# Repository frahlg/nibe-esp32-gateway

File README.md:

# NIBE ESP32 Gateway

An open-hardware ESP32-S3 board that plugs into the accessory bus of a NIBE
F-series heat pump (the MODBUS 40 port) and gives you local Wi-Fi access to it.
One 4-core cable to the pump carries both the data and the power. Order it fully
assembled from JLCPCB and print the box yourself.

Designed for the NIBE **F750**; the same port exists on F370, F470, F730,
F1145, F1155, F1245, F1255, SMO 40 and several VVM models.

> **Status: rev 1.0, design complete, not yet built.** The schematic and board
> pass KiCad's ERC and DRC, and every part was in stock at JLCPCB on 2026-11-25.
> Nobody has built a board or tested one on a heat pump yet. The ESPHome
> firmware in [`firmware/`](firmware) compiles but has not run on hardware. You can try
> it on the pump first with a [test rig](docs/test-rig.md) of shop-bought parts.

## What it does

- Talks to the heat pump on RS-485 the way a NIBE MODBUS 40 accessory does, so
  it works with the existing open-source gateways:
  [esphome-nibe](https://github.com/elupus/esphome-nibe),
  [NibeGW](https://www.openhab.org/addons/bindings/nibeheatpump/),
  [nibegw-esp](https://github.com/nptr/nibegw-esp) and the Home Assistant
  [Nibe Heat Pump](https://www.home-assistant.io/integrations/nibe_heatpump/)
  integration.
- Runs from the pump's own 12 V supply (AA3-X4:12), like MODBUS 40.
- USB-C for flashing and bench power.
- Protected against surges, reverse polarity and shorts on the pump cable.

| | |
|---|---|
| MCU | ESP32-S3-WROOM-1-N8R2 (Wi-Fi, Bluetooth LE, 8 MB flash, 2 MB PSRAM) |
| Bus | THVD1450 RS-485 transceiver, ±18 kV ESD, fail-safe receiver, PSM712 TVS, 120 Ω terminator on a cuttable jumper |
| Power | 12 V from the pump (9–18 V) or 5 V USB-C, TPS62933 buck to 3.3 V, PTC fuse, TVS |
| Connectors | 4-pin 3.5 mm pluggable terminal (12V, A, B, GND), USB-C |
| Other | RESET and BOOT buttons, PWR/STAT/BUS LEDs, unfitted 6-pin expansion header |
| Board | 50 × 58 mm, 2 layers |
| Box | 55 × 63 × 18 mm, two printed parts, 4 × M3 screws |

## Wiring

| Gateway | F750 terminal AA3-X4 |
|---|---|
| 12V | 12 |
| A | 11 |
| B | 10 |
| GND | 9 |

Then tick MODBUS 40 in the service menu (5.2 or 5.2.4). Full steps, with
safety notes, are in [docs/installation.md](docs/installation.md).

## Make one

1. **Board:** upload the files in [`hardware/production/`](hardware/production)
   to JLCPCB with assembly. See [docs/ordering.md](docs/ordering.md).
2. **Box:** print [`enclosure/base.stl`](enclosure/base.stl) and
   [`enclosure/lid.stl`](enclosure/lid.stl) in PETG or PLA, no supports.
3. **Firmware:** start from [`firmware/`](firmware) (pin map and an ESPHome
   configuration).
4. **Install:** [docs/installation.md](docs/installation.md).

## Documents

| | |
|---|---|
| [docs/installation.md](docs/installation.md) | Wiring to the F750, enabling MODBUS 40, troubleshooting |
| [docs/ordering.md](docs/ordering.md) | JLCPCB order, loose parts, printing, assembly |
| [docs/test-rig.md](docs/test-rig.md) | Try the firmware on the pump before you order boards, with an M5Stack Atom + Tail485 or a DevKitC rig |
| [docs/protocol.md](docs/protocol.md) | The NIBE accessory bus: electrical layer, frames, commands, timing, sources |
| [docs/design-notes.md](docs/design-notes.md) | Why each part is there, known gaps |
| [docs/schematic.pdf](docs/schematic.pdf) | Schematic |
| [hardware/README.md](hardware/README.md) | How the board is generated and checked |
| [enclosure/README.md](enclosure/README.md) | The box |
| [firmware/README.md](firmware/README.md) | Pin map, first flash |

## Repository

```
hardware/    board: Python source, generated KiCad project, production files
enclosure/   printable box: CadQuery source, STL and STEP
firmware/    pin map and a starting ESPHome configuration
docs/        installation, ordering, protocol, design notes, images
```

The board is generated from Python and checked by KiCad on every build, so a
change is: edit `hardware/generator/circuit.py`, run `hardware/build.sh`, read the
check results. See [hardware/README.md](hardware/README.md).

## Credits

This board stands on work by the NIBE open-source community: the openHAB
NibeGW gateway, esphome-nibe (elupus), NibePi (anerdins), nibegw-esp (nptr) and
the nibe Python library (yozik04). The protocol notes in
[docs/protocol.md](docs/protocol.md) come from their code and issue threads.

NIBE and MODBUS 40 are trademarks of NIBE AB. This project is not made or
endorsed by NIBE. Connecting third-party hardware to your heat pump is at your
own risk.

## Licence

- Hardware (board, schematic, enclosure): [CERN-OHL-P-2.0](LICENSE-HARDWARE)
- Software and scripts: [MIT](LICENSE-SOFTWARE)

---

### På svenska

Ett öppet ESP32-S3-kort som kopplas till tillbehörsbussen (MODBUS 40-porten) på
NIBE:s F-serie, till exempel F750. En 4-ledarkabel till plint AA3-X4 (12V, A, B,
GND) ger både data och ström. Kortet beställs färdigmonterat från JLCPCB med
filerna i `hardware/production/`, och lådan skrivs ut med 3D-skrivare från
`enclosure/`. Revision 1.0 är färdigritad och kontrollerad i KiCad men ännu inte
tillverkad eller testad på en värmepump. Mjukvaran är nästa steg.

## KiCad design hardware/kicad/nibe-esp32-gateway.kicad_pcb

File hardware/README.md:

# Hardware

The board is described in Python and turned into a normal KiCad 9 project. You
can open `kicad/nibe-esp32-gateway.kicad_pro` in KiCad and look at or edit
everything, but the next build overwrites hand edits. Change the Python, not the
KiCad files.

```
hardware/
├── build.sh                 build everything inside the official KiCad 9 Docker image
├── fetch-3d-models.sh       download KiCad 3D models (only for renders and STEP)
├── generator/
│   ├── circuit.py           THE CIRCUIT: parts, nets, schematic and board positions
│   ├── parts.py             part catalogue: symbol, footprint, LCSC number
│   ├── build.py             schematic, netlist check, ERC
│   ├── build_pcb.py         placement, routing, ground pours, silkscreen, DRC
│   ├── build_fab.py         Gerbers, drill, BOM, CPL, PDFs, STEP, renders
│   ├── schgen.py            writes .kicad_sch files
│   ├── pcbgen.py            pcbnew helpers
│   ├── router.py            small A* router (two layers, 45°, vias)
│   ├── fab.py               JLCPCB BOM/CPL and rotation corrections
│   ├── sexp.py              S-expression reader/writer
│   └── tools/               pins.py, footprint_pads.py, check_stock.py
├── kicad/                   generated KiCad project (schematic, board, project)
└── production/              generated files to order the board
```

## Build

You need Docker. Nothing else is installed on your machine.

```bash
cd hardware
./fetch-3d-models.sh   # optional, once: 3D models for renders and the STEP file
./build.sh             # schematic + board + production files
```

`./build.sh sch`, `./build.sh pcb` and `./build.sh fab` run one step each.

## What a build checks

Each step stops or reports when something is wrong:

1. **Netlist check.** The schematic is exported to a netlist with `kicad-cli`
   and compared pin by pin with `circuit.py`. Any difference stops the build.
2. **ERC** on the schematic (must report 0 issues).
3. **Routing.** Every net must route; failures are listed.
4. **DRC with schematic parity** on the board: clearances, unconnected items,
   and that the board matches the schematic. The build prints `DRC summary:
   clean` when all is well.

The enclosure has its own fit check against the board's STEP file (see
[../enclosure](../enclosure)).

## How the board is made

- **Schematic.** Every pin gets a short wire and a net label or power symbol.
  That keeps the generated drawing readable and easy to check.
- **Placement** is hand-written in `circuit.py`, in millimetres from the top-left
  corner of the board.
- **Routing.** A small grid router (`router.py`) routes one net at a time on a
  0.1 mm grid, or 0.05 mm next to 0.5 mm pitch pins. Power nets get wider
  tracks. Ground is not routed: both layers have a ground pour, each ground pad
  gets its own via just outside the pad, and stitching vias tie the pours
  together. The buck's SW and VBUCK nets are copper areas (`BUCK_ZONES` in
  `circuit.py`), not routed tracks.
- **No via in a pad.** The router never puts a via within 0.15 mm of an SMD pad
  of any net, and the build prints `via-in-pad check: 0 vias ...`.
- **Design rules** follow JLCPCB's standard 2-layer process: 0.2 mm clearance,
  0.25 mm signal tracks, 0.5–0.6 mm power tracks, 0.3/0.6 mm vias.

## Changing the circuit

1. Edit `circuit.py` (and `parts.py` for a new part).
2. `./build.sh` and read the output: netlist, ERC, routing, DRC.
3. Look at `docs/images/pcb-top.png` and `production/*.pdf`.
4. `python3 generator/tools/check_stock.py` before you order.

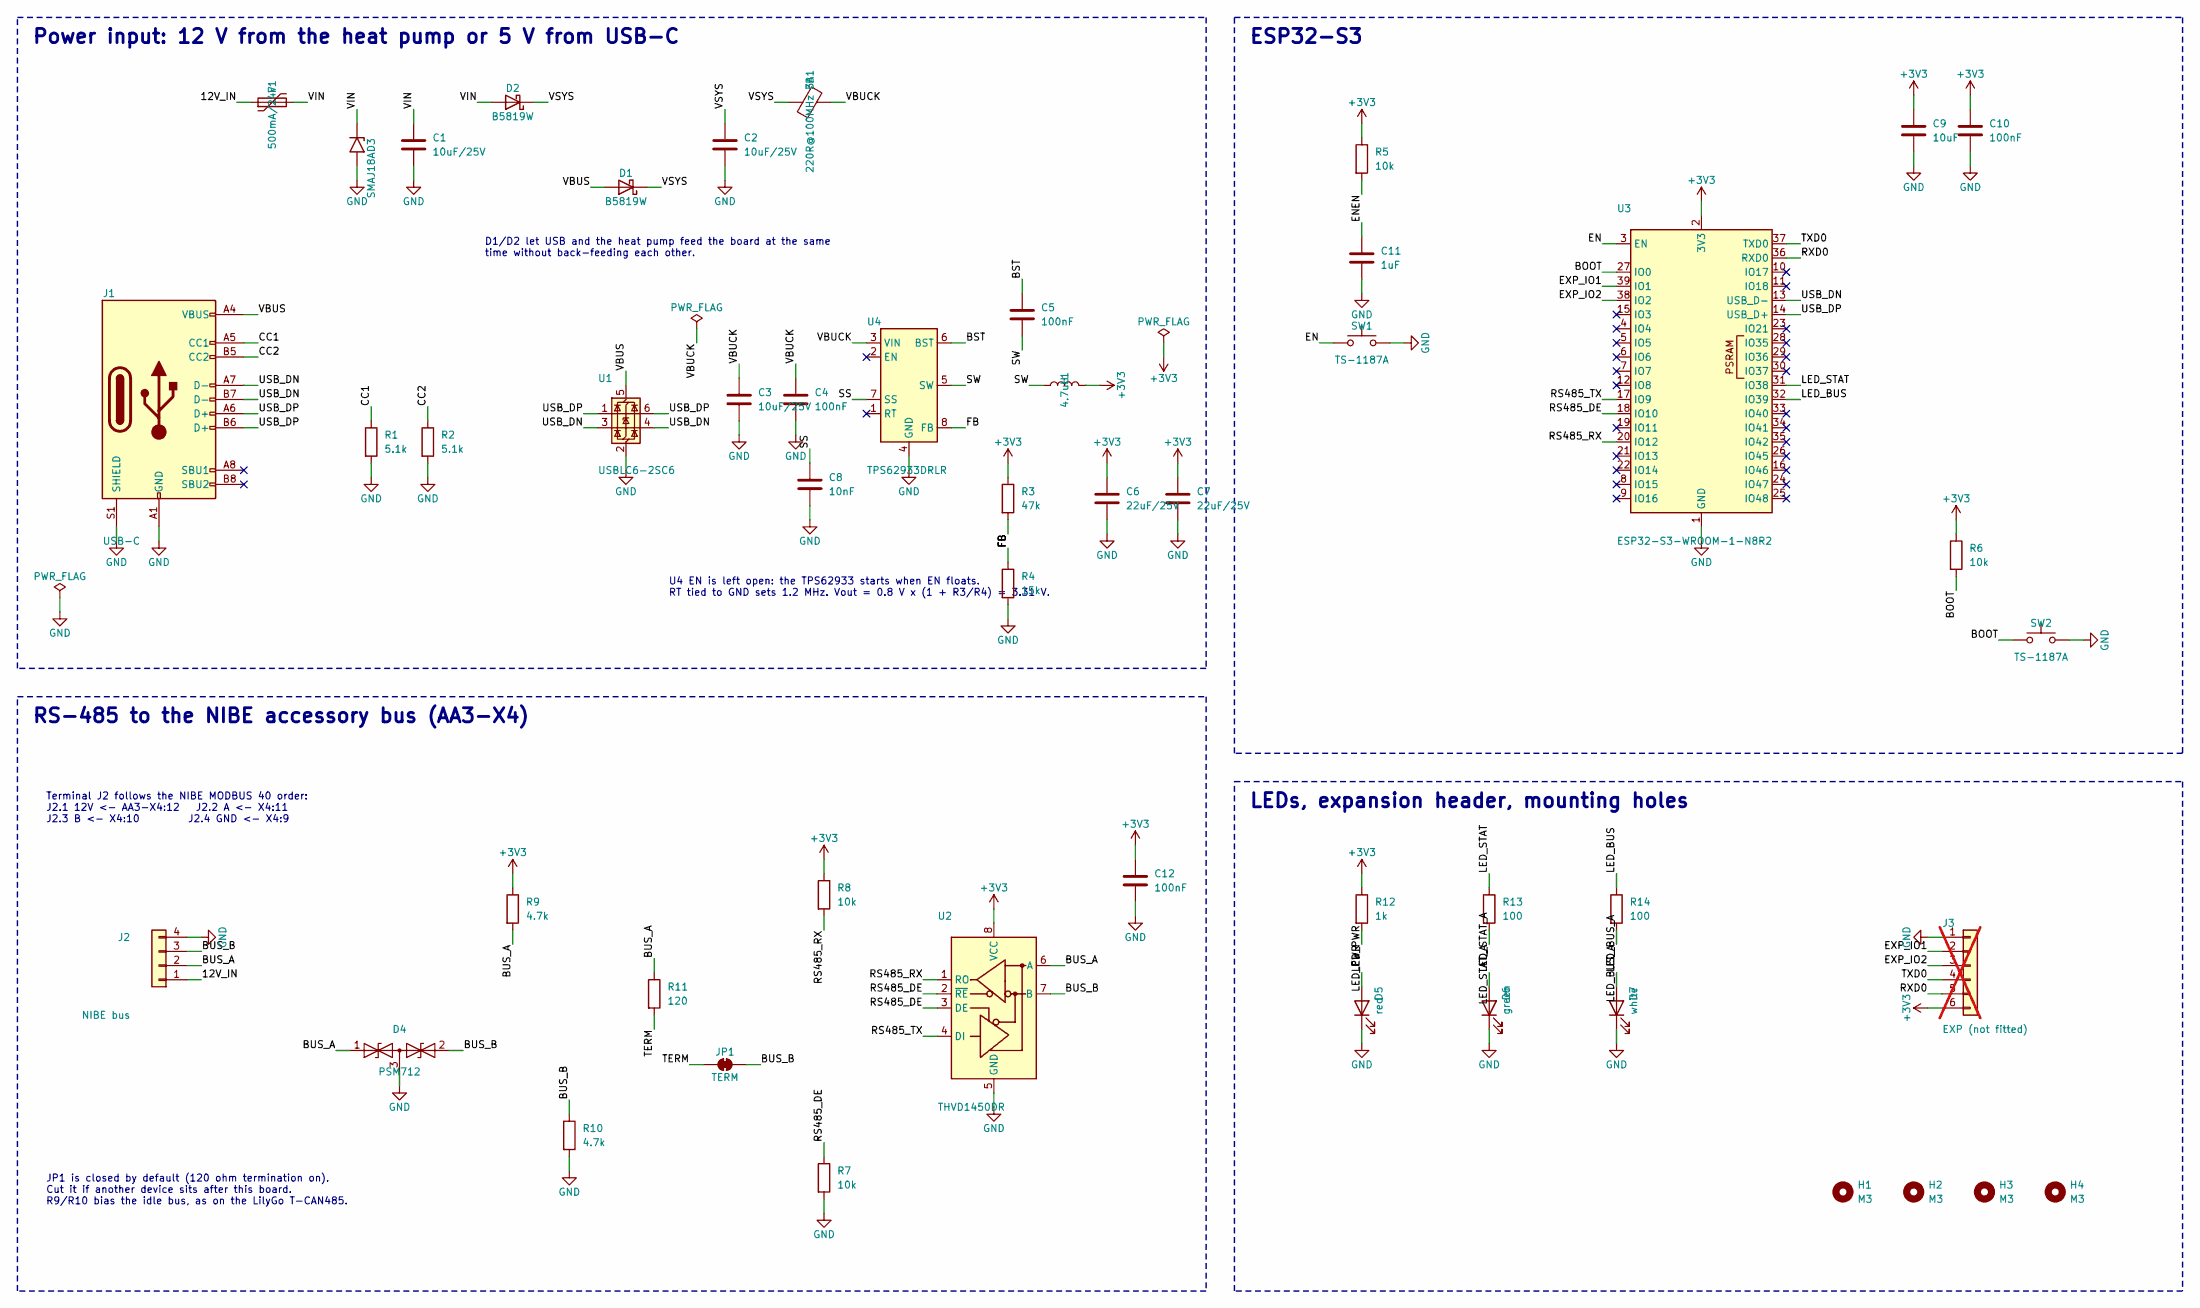
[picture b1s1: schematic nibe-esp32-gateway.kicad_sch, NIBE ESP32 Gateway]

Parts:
C1, C2, C3: 10uF/25V; C_0805_2012Metric; LCSC C15850
C4, C5, C10, C12: 100nF; C_0603_1608Metric; LCSC C14663
C6, C7: 22uF/25V; C_0805_2012Metric; LCSC C45783
C8: 10nF; C_0603_1608Metric; LCSC C57112
C9: 10uF; C_0603_1608Metric; LCSC C19702
C11: 1uF; C_0603_1608Metric; LCSC C15849
D1, D2: B5819W; D_SOD-123; MPN B5819W SL; LCSC C8598
D3: SMAJ18A; D_SMA; MPN SMAJ18A/TR13; LCSC C118306
D4: PSM712; SOT-23; MPN PSM712-LF-T7; LCSC C32677
D5: red; LED_0603_1608Metric; MPN KT-0603R; LCSC C2286
D6: green; LED_0805_2012Metric; MPN KT-0805G; LCSC C2297
D7: white; LED_0603_1608Metric; MPN KT-0603W; LCSC C2290
F1: 500mA/24V; Fuse_1206_3216Metric; MPN SMD1206P050TF/24; LCSC C492011
FB1: 220R@100MHz 3A; L_0805_2012Metric; MPN MPZ2012S221AT000; LCSC C76818
H1, H2, H3, H4: M3; MountingHole_3.2mm_M3
J1: USB-C; USB_C_Receptacle_HRO_TYPE-C-31-M-12; MPN TYPE-C-31-M-12; LCSC C165948
J2: NIBE bus; PhoenixContact_MC_1,5_4-G-3.5_1x04_P3.50mm_Horizontal; MPN DB2ERC-3.5-4P-GN; LCSC C395831
J3: EXP (not fitted); PinHeader_1x06_P2.54mm_Vertical; not fitted
JP1: TERM; SolderJumper-2_P1.3mm_Bridged_RoundedPad1.0x1.5mm
L1: 4.7uH; L_Changjiang_FNR4030S; MPN FNR4030S4R7MT; LCSC C167874
R1, R2: 5.1k; R_0603_1608Metric; LCSC C23186
R3: 47k; R_0603_1608Metric; LCSC C25819
R4: 15k; R_0603_1608Metric; LCSC C22809
R5, R6, R7, R8: 10k; R_0603_1608Metric; LCSC C25804
R9, R10: 4.7k; R_0603_1608Metric; LCSC C23162
R11: 120; R_0603_1608Metric; LCSC C22787
R12: 1k; R_0603_1608Metric; LCSC C21190
R13, R14: 100; R_0603_1608Metric; LCSC C22775
SW1, SW2: TS-1187A; SW_Push_1P1T_XKB_TS-1187A; MPN TS-1187A-B-A-B; LCSC C318884
U1: USBLC6-2SC6; SOT-23-6; MPN USBLC6-2SC6; LCSC C7519
U2: THVD1450DR; SOIC-8_3.9x4.9mm_P1.27mm; MPN THVD1450DR; LCSC C2671361
U3: ESP32-S3-WROOM-1-N8R2; ESP32-S3-WROOM-1; MPN ESP32-S3-WROOM-1-N8R2; LCSC C2913204
U4: TPS62933DRLR; SOT-583-8; MPN TPS62933DRLR; LCSC C3200405

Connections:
+3V3: C6.1, C7.1, C9.1, C10.1, C12.1, J3.6, L1.2, R3.1, R5.1, R6.1, R8.1, R9.1, R12.1, U2.8 (VCC), U3.2 (3V3)
/12V_IN: F1.1, J2.1
/BOOT: R6.2, SW2.1, U3.27 (IO0)
/BST: C5.1, U4.6 (BST)
/BUS_A: D4.1 (A1), J2.2, R9.2, R11.1, U2.6 (A)
/BUS_B: D4.2 (A2), J2.3, JP1.2 (B), R10.1, U2.7 (B)
/CC1: J1.A5 (CC1), R1.1
/CC2: J1.B5 (CC2), R2.1
/EN: C11.1, R5.2, SW1.1, U3.3 (EN)
/EXP_IO1: J3.2, U3.39 (IO1)
/EXP_IO2: J3.3, U3.38 (IO2)
/FB: R3.2, R4.1, U4.8 (FB)
/LED_BUS: R14.1, U3.32 (IO39)
/LED_BUS_A: D7.2 (A), R14.2
/LED_PWR: D5.2 (A), R12.2
/LED_STAT: R13.1, U3.31 (IO38)
/LED_STAT_A: D6.2 (A), R13.2
/RS485_DE: R7.1, U2.2 (~RE), U2.3 (DE), U3.18 (IO10)
/RS485_RX: R8.2, U2.1 (RO), U3.20 (IO12)
/RS485_TX: U2.4 (DI), U3.17 (IO9)
/RXD0: J3.5, U3.36 (RXD0)
/SS: C8.1, U4.7 (SS)
/SW: C5.2, L1.1, U4.5 (SW)
/TERM: JP1.1 (A), R11.2
/TXD0: J3.4, U3.37 (TXD0)
/USB_DN: J1.A7 (D-), J1.B7 (D-), U1.3 (I/O2), U1.4 (I/O2), U3.13 (USB_D-)
/USB_DP: J1.A6 (D+), J1.B6 (D+), U1.1 (I/O1), U1.6 (I/O1), U3.14 (USB_D+)
/VBUCK: C3.1, C4.1, FB1.2, U4.3 (VIN)
/VBUS: D1.2 (A), J1.A4 (VBUS), J1.A9 (VBUS), J1.B4 (VBUS), J1.B9 (VBUS), U1.5 (VBUS)
/VIN: C1.1, D2.2 (A), D3.1 (A1), F1.2
/VSYS: C2.1, D1.1 (K), D2.1 (K), FB1.1
GND: C1.2, C2.2, C3.2, C4.2, C6.2, C7.2, C8.2, C9.2, C10.2, C11.2, C12.2, D3.2 (A2), D4.3 (common), D5.1 (K), D6.1 (K), D7.1 (K), J1.A1 (GND), J1.A12 (GND), J1.B1 (GND), J1.B12 (GND), J1.S1 (SHIELD), J2.4, J3.1, R1.2, R2.2, R4.2, R7.2, R10.2, SW1.2, SW2.2, U1.2 (GND), U2.5 (GND), U3.1 (GND), U3.40 (GND), U3.41 (GND), U4.4 (GND)

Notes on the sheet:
Power input: 12 V from the heat pump or 5 V from USB-C
ESP32-S3
RS-485 to the NIBE accessory bus (AA3-X4)
LEDs, expansion header, mounting holes
Terminal J2 follows the NIBE MODBUS 40 order: J2.1 12V <- AA3-X4:12 J2.2 A <- X4:11 J2.3 B <- X4:10 J2.4 GND <- X4:9
JP1 is closed by default (120 ohm termination on). Cut it if another device sits after this board. R9/R10 bias the idle bus, as on the LilyGo T-CAN485.
U4 EN is left open: the TPS62933 starts when EN floats. RT tied to GND sets 1.2 MHz. Vout = 0.8 V x (1 + R3/R4) = 3.31 V.
D1/D2 let USB and the heat pump feed the board at the same time without back-feeding each other.

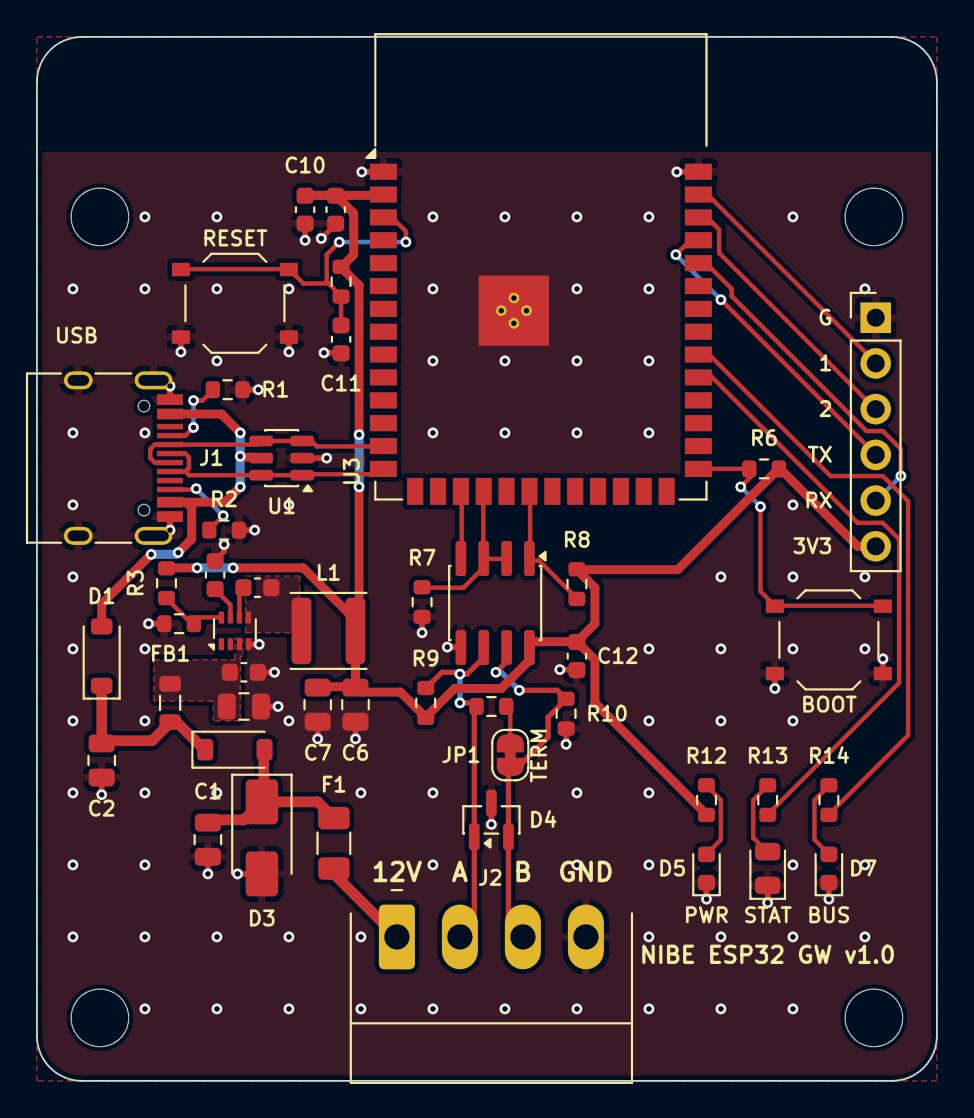
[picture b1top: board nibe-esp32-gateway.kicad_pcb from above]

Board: 2 copper layers, 50.0 x 58.0 mm, 50 parts (0 on the bottom side), 32 nets.

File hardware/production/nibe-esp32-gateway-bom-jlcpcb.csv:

Comment,Designator,Footprint,LCSC Part #
10uF/25V,"C1,C2,C3",C_0805_2012Metric,C15850
22uF/25V,"C6,C7",C_0805_2012Metric,C45783
10nF,C8,C_0603_1608Metric,C57112
10uF,C9,C_0603_1608Metric,C19702
100nF,"C4,C5,C10,C12",C_0603_1608Metric,C14663
1uF,C11,C_0603_1608Metric,C15849
B5819W,"D1,D2",D_SOD-123,C8598
SMAJ18A,D3,D_SMA,C118306
PSM712,D4,SOT-23,C32677
red,D5,LED_0603_1608Metric,C2286
green,D6,LED_0805_2012Metric,C2297
white,D7,LED_0603_1608Metric,C2290
500mA/24V,F1,Fuse_1206_3216Metric,C492011
220R@100MHz 3A,FB1,L_0805_2012Metric,C76818
USB-C,J1,USB_C_Receptacle_HRO_TYPE-C-31-M-12,C165948
NIBE bus,J2,"PhoenixContact_MC_1,5_4-G-3.5_1x04_P3.50mm_Horizontal",C395831
4.7uH,L1,L_Changjiang_FNR4030S,C167874
5.1k,"R1,R2",R_0603_1608Metric,C23186
47k,R3,R_0603_1608Metric,C25819
15k,R4,R_0603_1608Metric,C22809
10k,"R5,R6,R7,R8",R_0603_1608Metric,C25804
4.7k,"R9,R10",R_0603_1608Metric,C23162
120,R11,R_0603_1608Metric,C22787
1k,R12,R_0603_1608Metric,C21190
100,"R13,R14",R_0603_1608Metric,C22775
TS-1187A,"SW1,SW2",SW_Push_1P1T_XKB_TS-1187A,C318884
USBLC6-2SC6,U1,SOT-23-6,C7519
THVD1450DR,U2,SOIC-8_3.9x4.9mm_P1.27mm,C2671361
ESP32-S3-WROOM-1-N8R2,U3,ESP32-S3-WROOM-1,C2913204
TPS62933DRLR,U4,SOT-583-8,C3200405

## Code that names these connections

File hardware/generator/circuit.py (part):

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
# ---------------- LEDs and expansion --------------------------------------------------
add("R12", r0603("1k"), {"1": "+3V3", "2": "LED_PWR"}, sch=(256.54, 180.34, 0), pcb=(37.2, 42.4, 90))
add("D5", P["LED_R"], {"2": "LED_PWR", "1": "GND"}, sch=(256.54, 198.12, 90), pcb=(37.2, 46.2, 90), label="PWR")
add("R13", r0603("100"), {"1": "LED_STAT", "2": "LED_STAT_A"}, sch=(279.4, 180.34, 0), pcb=(40.6, 42.4, 90))
add("D6", P["LED_G"], {"2": "LED_STAT_A", "1": "GND"}, sch=(279.4, 198.12, 90), pcb=(40.6, 46.2, 90), label="STAT")
add("R14", r0603("100"), {"1": "LED_BUS", "2": "LED_BUS_A"}, sch=(302.26, 180.34, 0), pcb=(44.0, 42.4, 90))
add("D7", P["LED_W"], {"2": "LED_BUS_A", "1": "GND"}, sch=(302.26, 198.12, 90), pcb=(44.0, 46.2, 90), label="BUS")
add("J3", P["HDR6"], {"1": "GND", "2": "EXP_IO1", "3": "EXP_IO2",
                                                       "4": "TXD0", "5": "RXD0", "6": "+3V3"},
    sch=(365.76, 190.5, 0), pcb=(46.6, 15.6, 0), dnp=True)
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POWER_NETS = {"12V_IN": 0.6, "VIN": 0.6, "VSYS": 0.6, "VBUCK": 0.6, "VBUS": 0.5, "SW": 0.5, "+3V3": 0.5}

GPIO_MAP = [
    ("GPIO9", "RS485_TX", "UART TX to THVD1450 DI"),
    ("GPIO12", "RS485_RX", "UART RX from THVD1450 RO"),
    ("GPIO10", "RS485_DE", "Driver enable (DE and /RE), high = transmit"),
    ("GPIO38", "LED_STAT", "Green status LED, active high"),
    ("GPIO39", "LED_BUS", "White bus LED, active high"),
    ("GPIO0", "BOOT", "BOOT button, low = download mode at reset"),
    ("GPIO19/20", "USB D-/D+", "Native USB (Serial/JTAG) on USB-C"),
    ("GPIO1, GPIO2", "EXP_IO1/2", "Spare, on J3"),
    ("GPIO43/44", "TXD0/RXD0", "UART0, on J3"),
]

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

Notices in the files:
hardware/kicad/nibe-esp32-gateway.kicad_pcb:
Open hardware CERN-OHL-P-2.0  2026-11-25
